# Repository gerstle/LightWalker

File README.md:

LightWalker
===========

A production of the inappropirates
----------------------------------
Source code for the LightWalker.

What is it?
-----------
Just watch this - <http://www.youtube.com/watch?v=KcUk5MgrxwE>

LightWalker
-----------
This is a microcontroller sketch that runs on a teensy 3.2 (originally arduino mega) and handles...
*  bluetooth communications with the remote control
*  listening to sensors (microphone, accelerometer) and interpreting
*  making a bunch of RGB LEDs dance

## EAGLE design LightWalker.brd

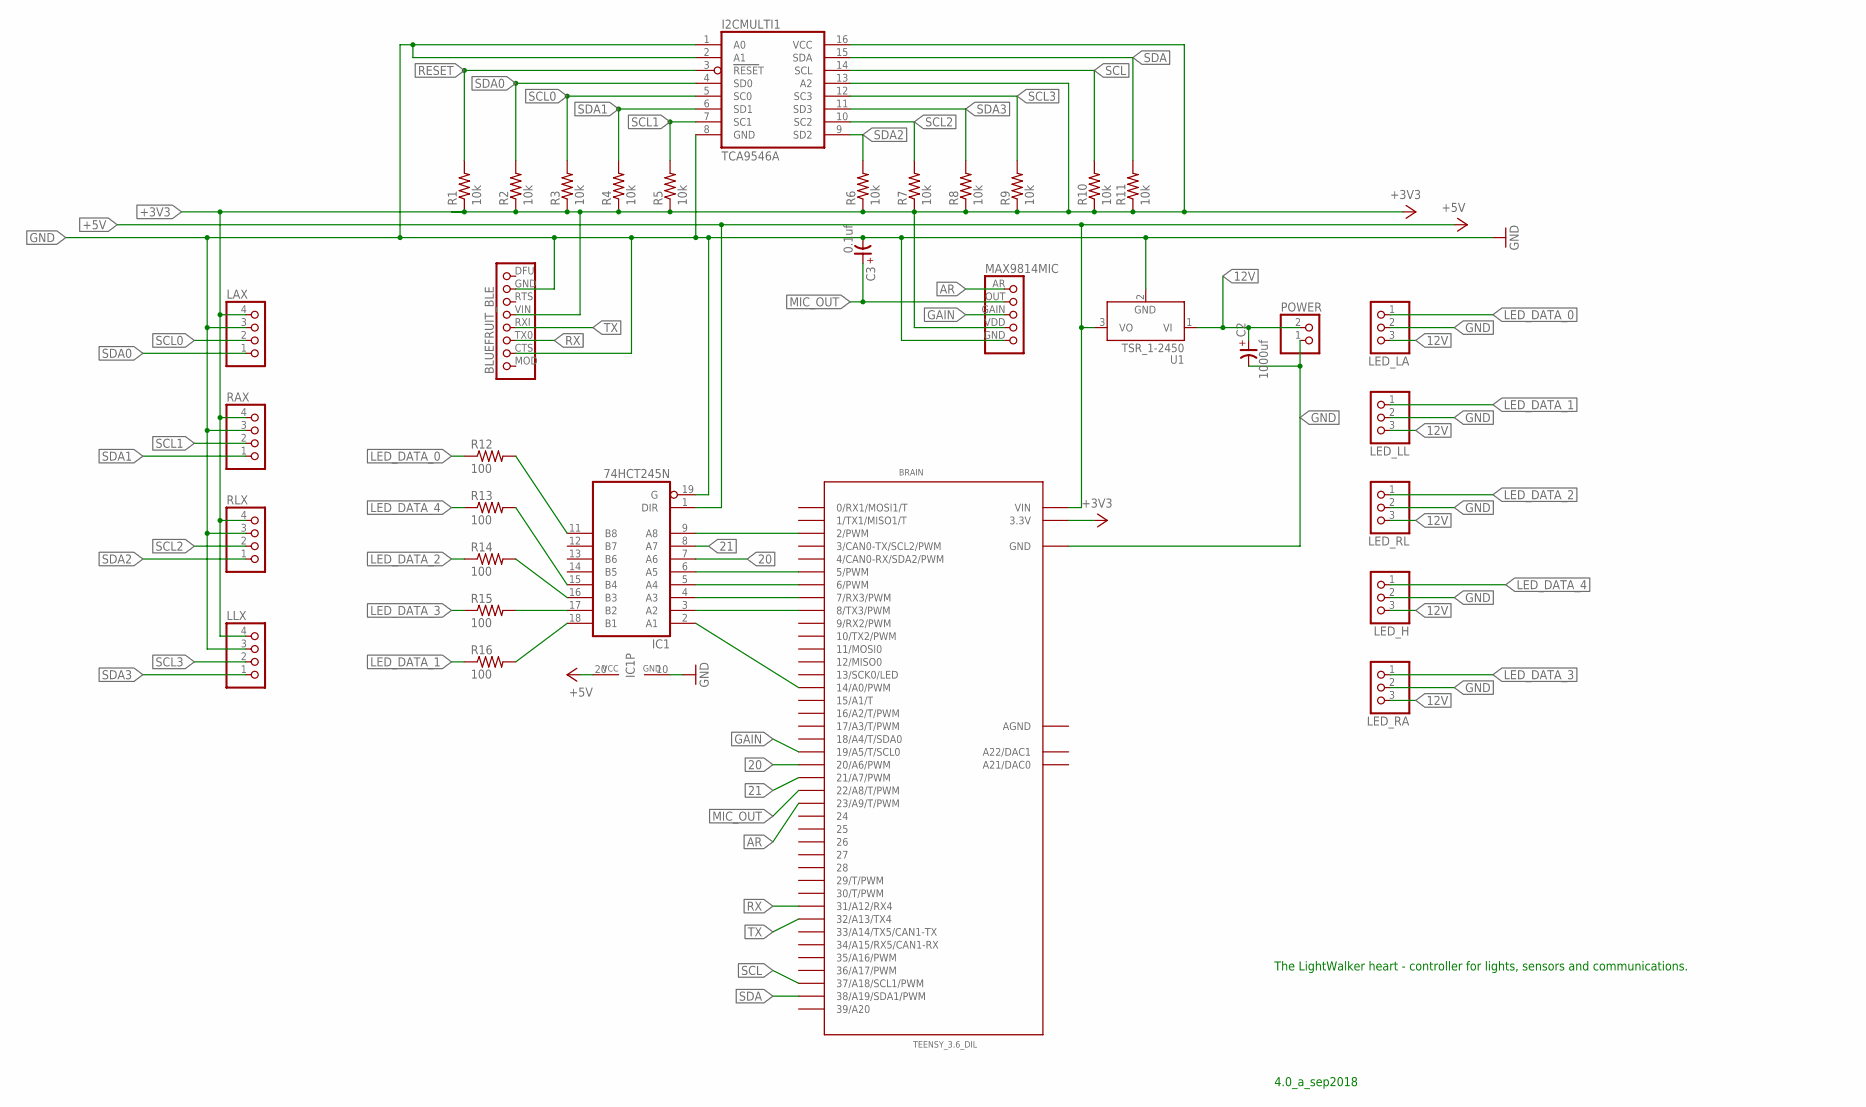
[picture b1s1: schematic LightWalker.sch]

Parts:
BRAIN: TEENSY_3.6_DIL
C2: 1000uf; SV-K
C3: 0.1uf; 3225
I2CMULTI1: TCA9546A; SOIC16_LONGPAD
IC1: 74HCT245N; DIL20
LAX: 2.54MM_TERMINAL_BLOCK-4; TB_1X4
LED_H: 2.54MM_TERMINAL_BLOCK-3; TB_1X3
LED_LA: 2.54MM_TERMINAL_BLOCK-3; TB_1X3
LED_LL: 2.54MM_TERMINAL_BLOCK-3; TB_1X3
LED_RA: 2.54MM_TERMINAL_BLOCK-3; TB_1X3
LED_RL: 2.54MM_TERMINAL_BLOCK-3; TB_1X3
LLX: 2.54MM_TERMINAL_BLOCK-4; TB_1X4
POWER: 2.54MM_TERMINAL_BLOCK-2; TB_1X2
R1, R2, R3, R4, R5, R6, R7, R8, R9, R10, R11: 10k; R1206
R12, R13, R14, R15, R16: 100; R1206
RAX: 2.54MM_TERMINAL_BLOCK-4; TB_1X4
RLX: 2.54MM_TERMINAL_BLOCK-4; TB_1X4
U1: TSR_1-2450; TSR-1
U$1: BLUEFRUIT_BLE_UART_FRIENDALL; BLUEFRUIT_BLE_UART_FRIEND_ALL
U$4: MAX9814MICALL; MAX9814MIC

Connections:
12V: C2.+, LED_H.3 (1), LED_LA.3 (1), LED_LL.3 (1), LED_RA.3 (1), LED_RL.3 (1), POWER.2 (1), U1.1 (VI)
20: BRAIN.20/A6 (20/A6/PWM), IC1.7 (A6)
21: BRAIN.21/A7 (21/A7/PWM), IC1.8 (A7)
+3V3: BRAIN.3.3V, BRAIN.3.3V3 (3.3V), I2CMULTI1.13 (A2), I2CMULTI1.16 (VCC), LAX.4, LLX.4, R1.1, R2.1, R3.1, R4.1, R5.1, R6.1, R7.1, R8.1, R9.1, R10.1, R11.1, RAX.4, RLX.4, U$1.VIN, U$4.VDD
+5V: BRAIN.VIN, IC1.1 (DIR), IC1.20 (VCC), U1.3 (VO)
AGND: BRAIN.AGND
AR: BRAIN.23/A9 (23/A9/T/PWM), U$4.AR
GAIN: BRAIN.19/A5 (19/A5/T/SCL0), U$4.GAIN
GND: BRAIN.GND, BRAIN.GND1 (GND), C2.-, C3.2 (-), I2CMULTI1.1 (A0), I2CMULTI1.2 (A1), I2CMULTI1.8 (GND), IC1.10 (GND), IC1.19 (G), LAX.3, LED_H.2, LED_LA.2, LED_LL.2, LED_RA.2, LED_RL.2, LLX.3, POWER.1 (2), RAX.3, RLX.3, U1.2 (GND), U$1.CTS, U$1.GND, U$4.GND
LED_DATA_0: LED_LA.1 (3), R12.1
LED_DATA_1: LED_LL.1 (3), R16.1
LED_DATA_2: LED_RL.1 (3), R14.1
LED_DATA_3: LED_RA.1 (3), R15.1
LED_DATA_4: LED_H.1 (3), R13.1
MIC_OUT: BRAIN.22/A8 (22/A8/T/PWM), C3.1 (+), U$4.OUT
unnamed: BRAIN.2 (2/PWM), IC1.9 (A8)
unnamed: BRAIN.5 (5/PWM), IC1.6 (A5)
unnamed: BRAIN.6 (6/PWM), IC1.5 (A4)
unnamed: BRAIN.7 (7/RX3/PWM), IC1.4 (A3)
unnamed: BRAIN.8 (8/TX3/PWM), IC1.3 (A2)
unnamed: IC1.11 (B8), R12.2
unnamed: IC1.15 (B4), R13.2
unnamed: IC1.16 (B3), R14.2
unnamed: IC1.17 (B2), R15.2
unnamed: IC1.18 (B1), R16.2
PIN14: BRAIN.14/A0 (14/A0/PWM), IC1.2 (A1)
RESET: I2CMULTI1.3 (RESET), R1.2
RX: BRAIN.31/A12 (31/A12/RX4), U$1.TX0 (TXO)
SCL: BRAIN.37/A18 (37/A18/SCL1/PWM), I2CMULTI1.14 (SCL), R10.2
SCL0: I2CMULTI1.5 (SC0), LAX.2, R3.2
SCL1: I2CMULTI1.7 (SC1), R5.2, RAX.2
SCL2: I2CMULTI1.10 (SC2), R7.2, RLX.2
SCL3: I2CMULTI1.12 (SC3), LLX.2, R9.2
SDA: BRAIN.38/A19 (38/A19/SDA1/PWM), I2CMULTI1.15 (SDA), R11.2
SDA0: I2CMULTI1.4 (SD0), LAX.1, R2.2
SDA1: I2CMULTI1.6 (SD1), R4.2, RAX.1
SDA2: I2CMULTI1.9 (SD2), R6.2, RLX.1
SDA3: I2CMULTI1.11 (SD3), LLX.1, R8.2
TX: BRAIN.32/A13 (32/A13/TX4), U$1.RXI

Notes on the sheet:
The LightWalker heart - controller for lights, sensors and communications.
4.0_a_sep2018

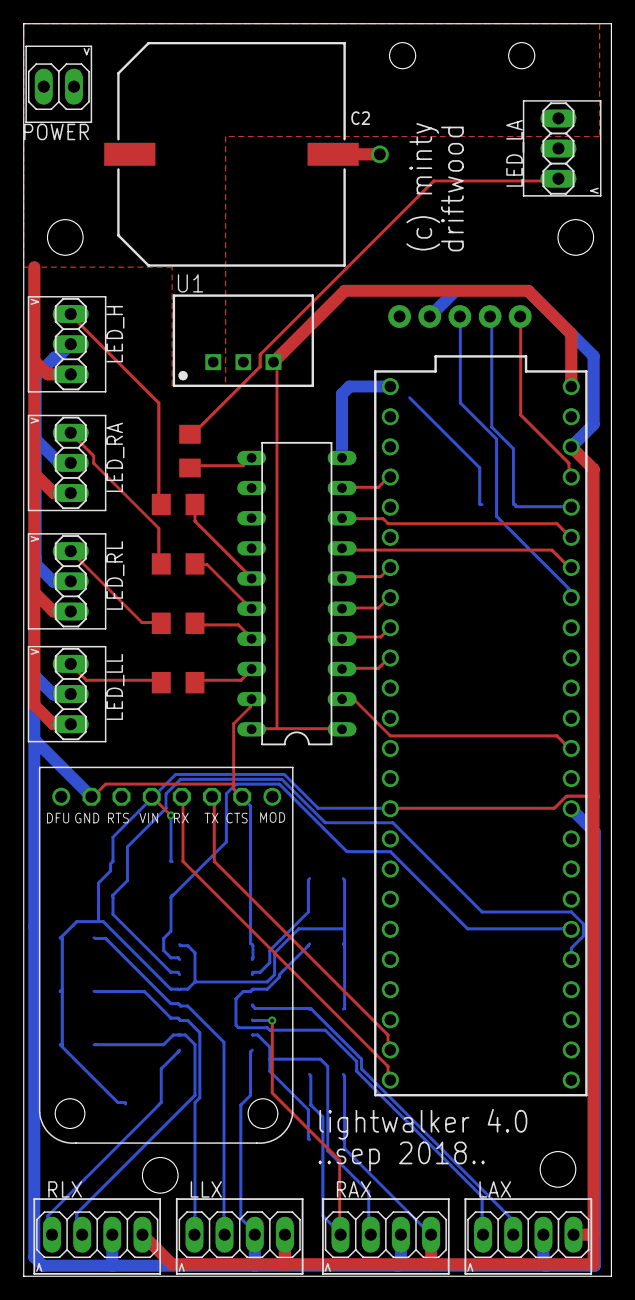
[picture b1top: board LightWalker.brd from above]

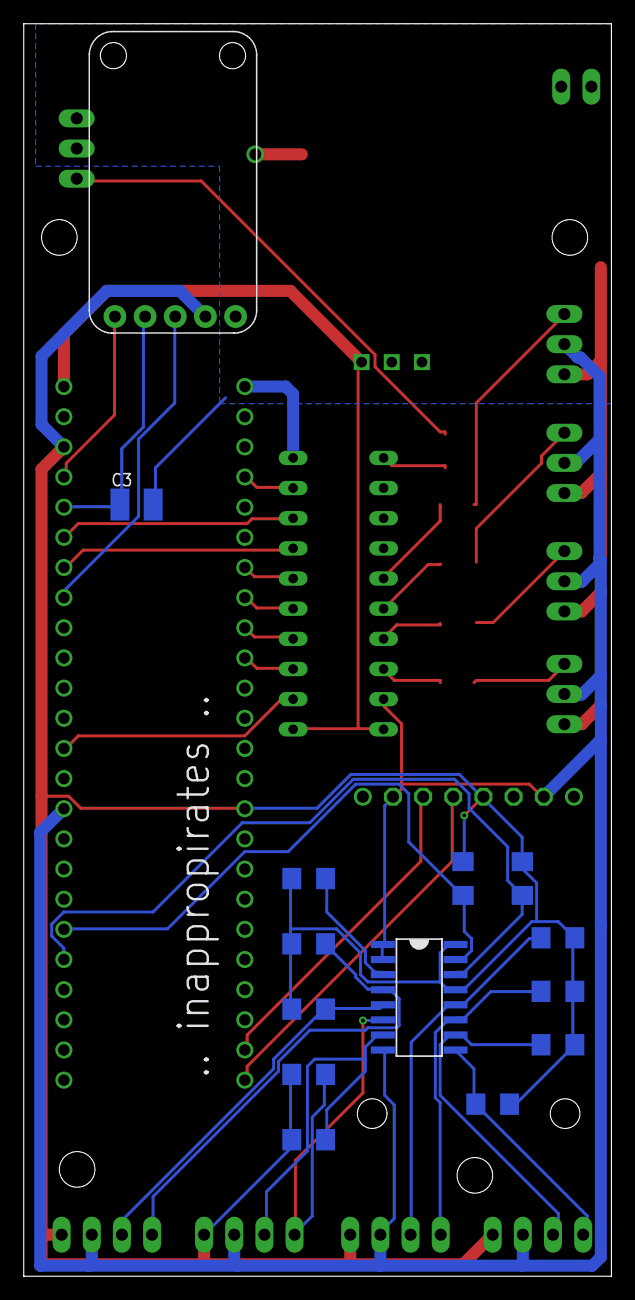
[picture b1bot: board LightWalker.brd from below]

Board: 2 copper layers, 49.5 x 105.5 mm, 34 parts (14 on the bottom side), 38 nets.

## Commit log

2013-01-26 Initializing
2013-01-26 My first two shots at TLC's developer shield, lights, and arduino
2013-01-26 this is Christopher De Vries' www.idolstarastronomer.com site
2013-01-26 testing stuff from breadboard
2013-01-27 first iteration of an example leg with a simple on/off flash
2013-01-28 Fails on loading more legs into the _legs vector. I'm gonna strip out the vectors and go back to static arrays, but I wanted to save this cause it compiles and runs, but definitely has memory issues.
2013-01-28 Working flash & sparkle on 2 legs. Also converted to static arrays for legs and pixels
2013-02-01 some random stuff, but mostly my stepdetect first shot
2013-02-02 introduction of detectStepAverageSpike function
2013-02-04 first stilt test
2013-02-15 re-org and new bluetooth code for android and arduino
2013-02-17 decent working bluetooth comms
2013-02-18 First real shot of tying the android remote control to the light walker and being able to control it. Not fully implemented
2013-02-21 remote control now setup as a solid preferences based tool. fixed global brightness setting in lightwalker. etc. etc. etc.
2013-02-25 random checkout so I have code remote this week.
2013-02-27 added discrete colors, updated application of max brightness, etc.
2013-03-06 messaging setup between bluetooth and arduino including changing configs. Also rounded out pulse mode
2013-03-19 multiplexing & accelerometer tests
2013-04-05 big ol' massive commit w/ equalizer stuff and more
2013-04-05 fix merge
2013-04-09 android & arduino sound working
2013-04-09 sound on the arduino
2013-04-10 missed these two...
2013-06-01 working 4x multiplexing test, lightwalker readme of final configuration, etc
2013-06-03 switch to mega, bluetooth fixes, addition of 4 adxl
2013-06-03 add gravity settings, audio changes
2013-06-05 back to string communications, but with progmem
2013-06-06 revert to text for communications, add some delays
2013-06-06 got all the accelerometer stuff working for now. gravity still needs to listen to its color settings and what not
2013-06-06 fix use of class currentTime variable
2013-06-30 blah
2013-06-30 pulse stuff (no off) + remotecontrol only sending colors in increments of 17
2013-07-01 I think I fixed EQ! added 'all bands' setting and switched to exponential moving average
2013-07-29 transition to 4 legs w/ different pixel lengths.
2013-08-04 rainbow pattern
2013-08-12 FIRST FULL WALK!
2013-08-16 enable turning off leg stilts and arms + some cleanup
2013-08-16 rainbow EQ!
2013-10-06 cleanup
2013-10-07 hopefully helps with gerstle/LightWalker#3
2013-10-07 fixes gerstle/lightwalker#7
2013-10-07 some stuff for gerstle/lightwalker#5 and other stuff
2013-10-08 fixes gerstle/lightwalker#16 - default mode
2013-10-08 bubble mode woohoo.
2013-10-09 readme update
2013-10-17 speed up and fix bubble mode
2013-10-18 Add horns with lights. Oh yeah.
2013-10-18 fix broken pixels on back of legs for sparkle
2014-01-03 make the color picker bigger and cleanup
2014-01-31 Move to teensy + Move to fastLED + huge re-write of modes
2014-02-03 new audio with software instead of hardware
2014-02-03 finish up some audio stuff + introduce stepping into rainbow mode
2014-02-05 First pass at zebra mode, some cleanup, and some equalizer work
2014-02-08 switch from FastLED2 to 2.1
2014-03-01 put bluetooth selection back & some tools
2014-03-01 add fps
2014-03-01 remove serial.print
2014-03-02 First arduino *and* teensy compatible codebase on FastLED2.1
2014-03-02 add ignore file
2014-03-02 updating ignore
2014-03-02 removing ignored files
2014-03-02 update ignore
2014-03-02 set ff=unix
2014-03-30 +flames, other fixes
2014-04-28 +perlins noise on equalizer, +flames update to Kriegsman's
2014-05-09 Add perlin noise to rainbow mode
2014-10-21 +HSV setTransitionColor
2014-10-25 +chaos, change equalizer to use inoise
2014-10-25 chaos updates
2014-10-25 make sparkle.shimmer more shimmery
2014-10-25 +chaos mode
2014-10-25 default preference updates
2014-10-25 I don't remember :)
2015-07-28 update some sparkle stuff
2016-03-09 chaos defaults
2016-03-09 initial schema for pcb
2016-03-15 LightWalker board 3.0, march 2016. printed.
2016-03-23 remove main mode as new remote app doesn't use it
2016-03-23 yay, no more crappy app
2016-03-23 more cleanup
2016-03-23 up the read the me.
2016-03-27 lightwalker 3.0 testing stuff
2016-04-06 gitignore update
2016-04-06 reorganization and setup w/ eclipse arduino plugin
2016-04-06 I don't know about this egit thing...
2016-04-20 initial 3.0 board
2016-04-20 kinda getting the new mic working...
2018-03-14 just syncing... think this has adding of the spine lights
2018-10-29 lightwalker PCB 4.0
2018-11-06 migrate to BLE and handle some pin changes
2018-11-07 initial octo setup, def not final
2018-11-26 midway through migration to new approach, chaos and eq mode working
2018-11-27 finish transitioning modes over to new style, -pulse
2019-07-27 sloeber setup steps
2024-08-05 Use platform, minor tweaks
2024-08-09 Move the leg half, tweek ble connect delay, sparklemode tweak
2024-08-15 move arm halfway point forward
